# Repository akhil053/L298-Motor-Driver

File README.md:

# L298-Motor-Driver
This project focuses on the design of a DC motor driver PCB using the L298N motor driver IC.  The schematic and PCB layout were developed in KiCad with proper component placement, routing, and net labeling.  The design was validated using ERC and DRC checks and is ready for fabrication.

# MotorLink – DC Motor Driver PCB Design

## Description
This project involves the design of a DC motor driver PCB using the L298N motor driver IC. 
The schematic and PCB layout were developed using KiCad.

## Features
- Forward and reverse motor control
- Proper net labeling and routing
- Compact PCB layout

## Tools Used
- KiCad

## Design Validation
- Performed ERC (Electrical Rule Check)
- Performed DRC (Design Rule Check)

## Files Included
- Schematic design files
- PCB layout files
- (Optional) Gerber files for fabrication

## Preview
(Add images here)

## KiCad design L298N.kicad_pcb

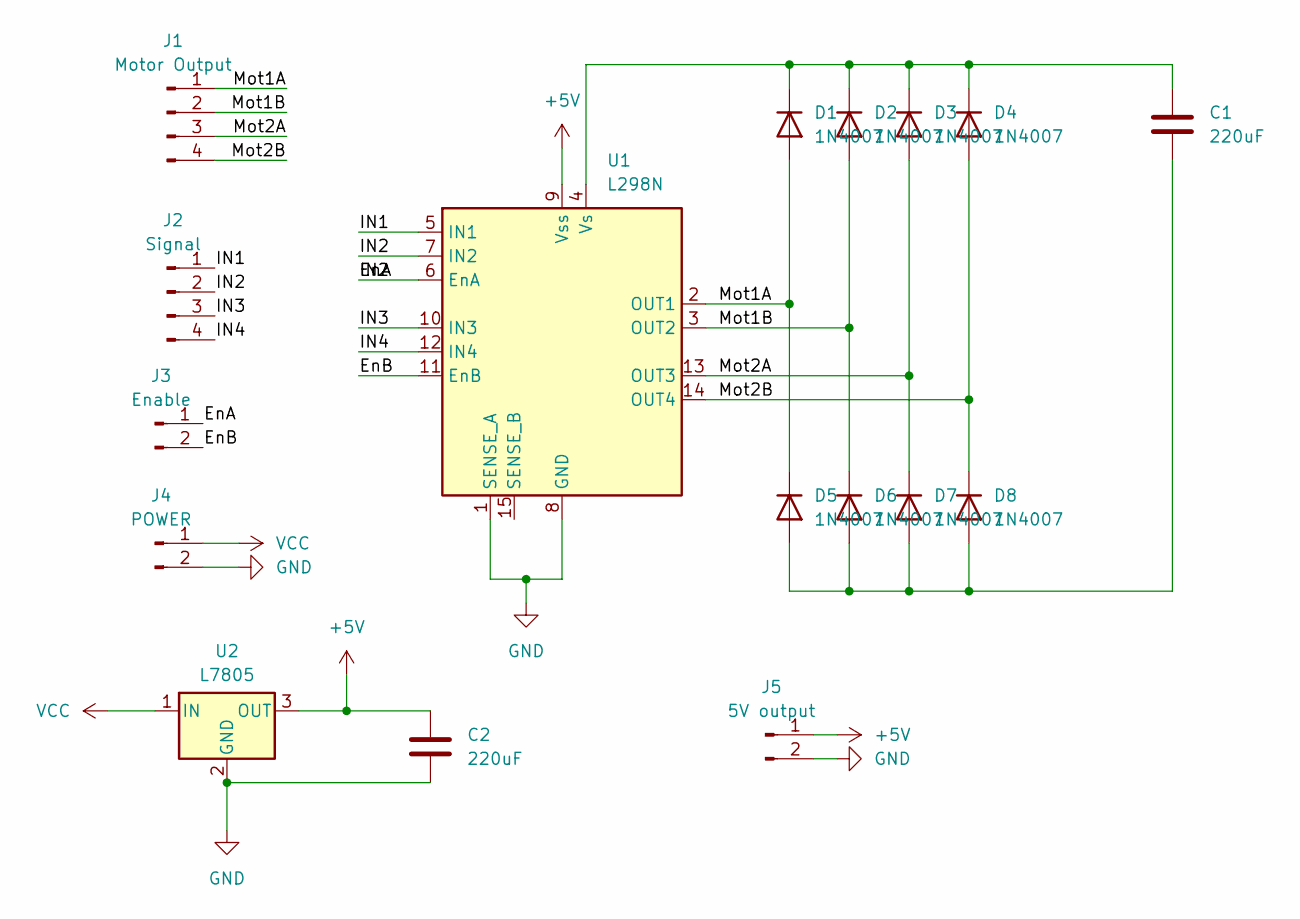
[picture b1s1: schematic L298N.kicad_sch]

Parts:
C1, C2: 220uF; C_Radial_D10.0mm_H12.5mm_P5.00mm
D1, D2, D3, D4, D5, D6, D7, D8: 1N4007; D_SOD-128
J1: Motor Output; TerminalBlock_Phoenix_MKDS-1,5-4-5.08_1x04_P5.08mm_Horizont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
J2: Signal; TerminalBlock_Phoenix_MKDS-1,5-4-5.08_1x04_P5.08mm_Horizont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
J3: Enable; TerminalBlock_Phoenix_MKDS-1,5-2-5.08_1x02_P5.08mm_Horizont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
J4: POWER; TerminalBlock_Phoenix_MKDS-1,5-2-5.08_1x02_P5.08mm_Horizont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
J5: 5V output; TerminalBlock_Phoenix_MKDS-1,5-2-5.08_1x02_P5.08mm_Horizont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
U1: L298N; TO-220-15_P2.54x5.08mm_StaggerOdd_Lead4.58mm_Vertical
U2: L7805; TO-252-2

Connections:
+5V: C2.1, J5.1, U1.9 (Vss), U2.3 (OUT)
/EnA: J2.2, J3.1, U1.6 (EnA), U1.7 (IN2)
/EnB: J3.2, U1.11 (EnB)
/IN1: J2.1, U1.5 (IN1)
/IN3: J2.3, U1.10 (IN3)
/IN4: J2.4, U1.12 (IN4)
/Mot1A: D1.2 (A), D5.1 (K), J1.1, U1.2 (OUT1)
/Mot1B: D2.2 (A), D6.1 (K), J1.2, U1.3 (OUT2)
/Mot2A: D3.2 (A), D7.1 (K), J1.3, U1.13 (OUT3)
/Mot2B: D4.2 (A), D8.1 (K), J1.4, U1.14 (OUT4)
GND: C2.2, J4.2, J5.2, U1.1 (SENSE_A), U1.8 (GND), U2.2 (GND)
unnamed: C1.1, D1.1 (K), D2.1 (K), D3.1 (K), D4.1 (K), U1.4 (Vs)
unnamed: C1.2, D5.2 (A), D6.2 (A), D7.2 (A), D8.2 (A)
VCC: J4.1, U2.1 (IN)

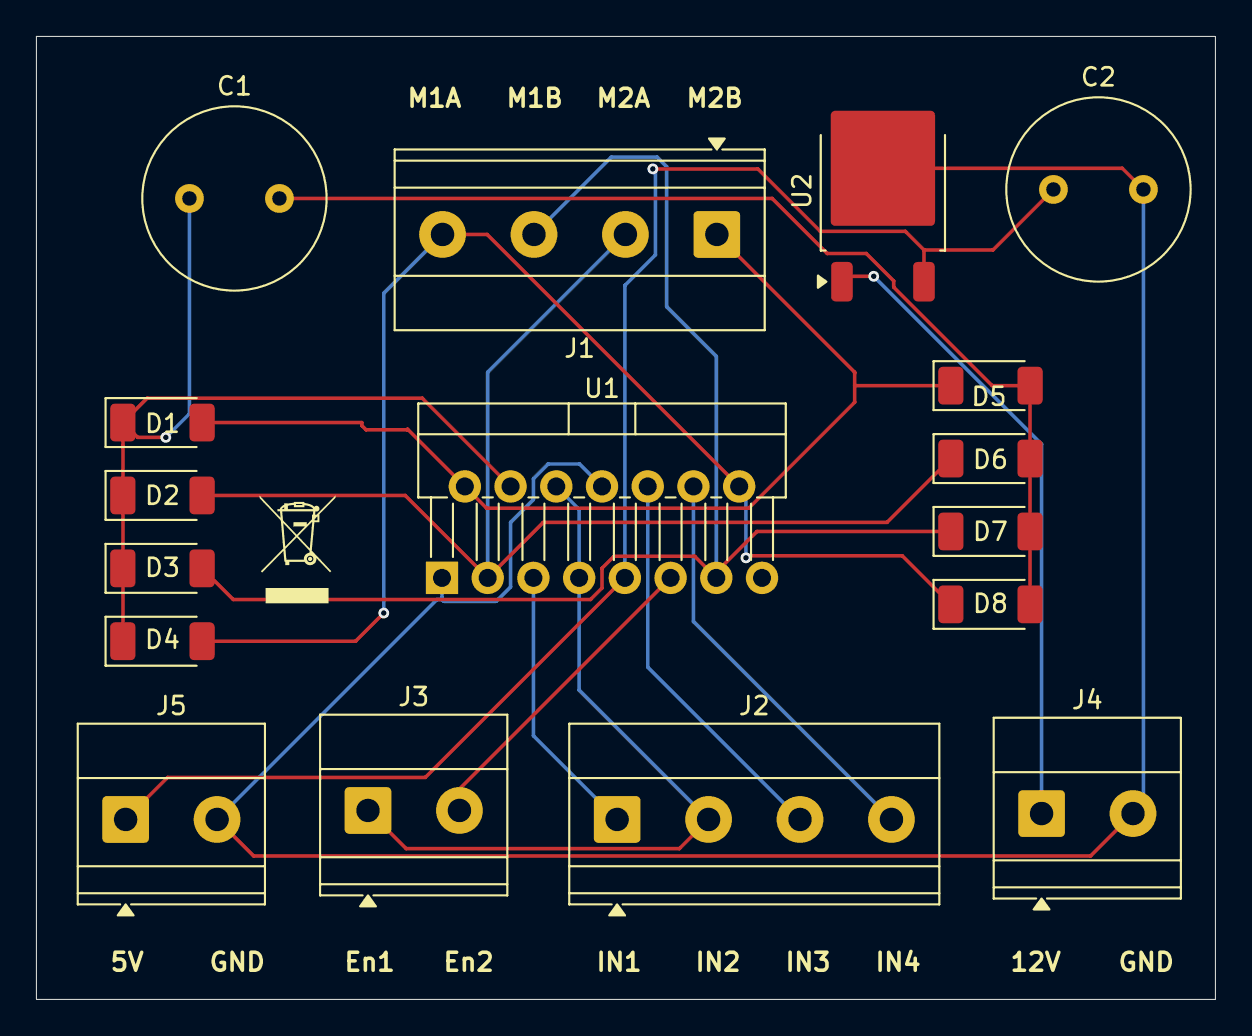
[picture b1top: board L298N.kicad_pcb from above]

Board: 2 copper layers, 65.5 x 53.5 mm, 17 parts (0 on the bottom side), 14 nets.

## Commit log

2026-04-05 Create Gerber and Drill files
